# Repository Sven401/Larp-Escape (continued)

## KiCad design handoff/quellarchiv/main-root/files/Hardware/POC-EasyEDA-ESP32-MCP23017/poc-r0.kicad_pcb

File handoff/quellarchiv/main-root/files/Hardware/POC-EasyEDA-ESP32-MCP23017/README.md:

# ESP32–MCP23017-I²C-POC, Entwurf POC-R0

**Stand 2026-10-10:** elektrischer Vorentwurf, nicht gefertigt und nicht fertigungsbereit. `poc-r0.kicad_pcb` ist eine editierbare KiCad-5.1-PCB-Datei (Formatversion `20171130`) mit 19 Footprints, 116 Pads, 30 benannten Netzen und geschlossenem 110 × 80-mm-Umriss. **Sie hat null Leiterbahnen und Platzhalter-Footprints für SW1–SW3.** `netzliste.csv` ist eine von Hand erstellte Soll-Netzliste, kein CAD-Export. Die SVGs sind editierbare Vektoransichten, keine CAD-Schaltpläne. Es gibt noch keinen nativen EasyEDA-Pro-Schaltplan und kein ERC-Ergebnis. Der EasyEDA-DRC des importierten PCBs meldete 88 offene Verbindungen.

## Quellenbasis und Abgrenzung

- Produkt-Hauptcheckout `main` / `29da937c4309beddfd45c5dd0fbf84fdf853d8e4`, am 2026-10-10 geprüft. Die 15 älteren Dateien in `Hardware/` sind unveränderte Eingangsquellen; insbesondere ihre Beschriftungen belegen keine reale Originalbox-Verdrahtung.
- Vergleich: `.hardware-interface-worktree/Hardware/SCHNITTSTELLENABGLEICH-2026-10-10.md` auf `plan/hardware-revision-schnittstellenabgleich` / `853dd06423d52eec30d93f394b21280903c128d1`; Firmware-Pins in `.hardware-diagnostic-worktree/src/GameConfiguration/StandardProfile.cpp` und `lib/MCPConfig/MCPConfig.cpp` auf `db52d7aa318a96e24e97e6b62194df644b9758e2`. Der POC bildet **einen** Expander ab, nicht die zwei Expander der Originalbox.
- [Espressif DevKitC V4, Steckerbelegung und Versorgung](https://docs.espressif.com/projects/esp-dev-kits/en/latest/esp32/esp32-devkitc/user_guide.html), [ESP32-WROOM-32E](https://documentation.espressif.com/esp32-wroom-32e_esp32-wroom-32ue_datasheet_en.html), [ESP32-Hardware-Designrichtlinien](https://documentation.espressif.com/esp-hardware-design-guidelines/en/latest/esp32/index.html), [Microchip MCP23017 DS20001952D](https://ww1.microchip.com/downloads/aemDocuments/documents/APID/ProductDocuments/DataSheets/MCP23017-Data-Sheet-DS20001952.pdf).
- EasyEDA Pro V3.2.149 ist als lokale GUI verfügbar. Am 2026-10-10 wurde `poc-r0.kicad_pcb` über **Import > KiCad** in ein EasyEDA-Pro-Projekt `poc-r0` importiert. Umriss, Footprints und Ratlines waren in der PCB-Ansicht sichtbar. Der Import ist keine vollständige elektrische oder mechanische Validierung. Die Bridge-Erweiterung v0.1.1 wurde ebenfalls importiert, ihre externe Interaktionsberechtigung ist jedoch nicht freigeschaltet; `easyeda_doctor` meldete deshalb `disconnected` am lokalen Port 18765. Eine CLI wurde nicht gefunden. Das [V3-Dateiformat](https://prodocs.easyeda.com/en/format/index/) ist ein projektgebundenes Logformat; die kanonische PoC-Quelle bleibt bis zu einem geprüften nativen Export die KiCad-Datei.

## Architekturentscheidung

X1 ist **ESP32-DevKitC V4 mit ESP32-WROOM-32E**, als steckbare Baugruppe auf zwei 19-poligen Buchsenleisten. Der DevKit übernimmt USB, Spannungsregler, USB-UART und seine vorhandenen EN-/BOOT-Funktionen. Diese Entscheidung vermeidet im POC ein ungeprüftes eigenes HF-Layout für das WROOM-Modul. Ein beliebiges als „ESP32 DevKit“ verkauftes Board ist kein freigegebener Ersatz: Steckerabstand, Bestückungsseite und USB-Überstand sind vor dem PCB-Footprint gegen genau das beschaffte DevKit und Espressifs Maßzeichnung zu prüfen.

X1 wird ausschließlich über seinen USB-Anschluss versorgt. Der 5-V-Stift J2/19 des DevKit bleibt unbeschaltet. U1 (MCP23017-E/SP, 28-poliges SPDIP) erhält 3,3 V von X1 J2/1. Keine externe 3,3-V-Einspeisung, kein 5-V-I/O und keine Leistungslast an den GPIO-Klemmen. Der verfügbare 3,3-V-Strom des konkret beschafften DevKit und die Last des späteren Aufbaus sind noch nicht gemessen oder budgetiert; die POC-Klemmen sind nur für hochohmige Logik-/Messanschlüsse vorgesehen.

SDA = ESP GPIO21, SCL = GPIO22, beide mit je 4,7 kΩ nach 3,3 V. Das entspricht der geprüften Firmware-Konfiguration. U1 A2/A1 liegen auf GND; A0 hat 10 kΩ Pulldown. Ohne Shunt JP1: 0x20; mit JP1 nach 3,3 V: 0x21. JP1 darf nur spannungslos umgesteckt werden. Der Firmwarestand der Originalbox erwartet gleichzeitig 0x20 und 0x21; ein Lauf dieser Firmware auf diesem POC würde daher keine vollständige Box simulieren.

SW1 zieht X1 EN nach GND (Reset), SW2 zieht GPIO0 nach GND (Boot), SW3 zieht U1 RESET nach GND. R3/R5/R6 sind je 10 kΩ Pull-ups; R5/R6 ergänzen die DevKit-Beschaltung und müssen gegen das genaue Board-Schaltbild geprüft werden. C1 100 nF direkt an U1 VDD/VSS, C2 10 µF an der lokalen 3,3-V-Schiene. Keine Interruptleitung ist zum ESP verdrahtet; INTA/INTB sind nur auf J5 herausgeführt. Sie brauchen vor Nutzung eine definierte elektrische Konfiguration und bei Open-Drain-Betrieb einen Pull-up.

## Pin-/Bus-/Versorgungsvertrag POC-HW/0.1-draft

| Signal | Quelle → Ziel | Pegel / Richtung | Status |
| --- | --- | --- | --- |
| +3V3 | X1 DevKit J2/1 → U1/9, Pull-ups, C1/C2 | 3,3 V, USB-abgeleitet | Entwurf; Stromreserve offen |
| GND | X1 J2/14 und J3/1,7 → U1/10, Taster, C1/C2 | gemeinsamer Rückleiter | Entwurf |
| SDA | X1 J3/6 GPIO21 → U1/13 | I²C, Open Drain, 4,7 kΩ nach 3,3 V | Quellkonfiguration abgeglichen |
| SCL | X1 J3/3 GPIO22 → U1/12 | I²C, 4,7 kΩ nach 3,3 V | Quellkonfiguration abgeglichen |
| EN / BOOT | X1 J2/2 / J3/14 → SW1 / SW2 nach GND | aktive LOW-Taster; GPIO0 ist Strap-Pin | nur POC, nicht Boxbeleg |
| MCP_RESET | U1/18 → SW3 nach GND, R3 nach 3,3 V | aktiv LOW | Entwurf |
| A0/A1/A2 | U1/15 /16 /17 | 0x20 oder 0x21 per JP1; A1=A2=LOW | Entwurf |
| GPA0…GPA7 | U1/21…28 → J3/1…8 | 3,3-V-GPIO | GPA7 laut Microchip nur als Ausgang einplanen |
| GPB0…GPB7 | U1/1…8 → J4/1…8 | 3,3-V-GPIO | GPB7 laut Microchip nur als Ausgang einplanen |
| INTA/INTB | U1/20 /19 → J5/1 /2 | noch kein Pull-up/ESP-Eingang | Fähigkeit offen |
| ESP-GPIO23/19/18/17 | X1 J3/2/8/9/11 → J6/1…4 | 3,3-V-GPIO | POC-Breakout; GPIO17 nur bei WROOM-Variante |

J5/3 = 3,3 V, J5/4 = GND; J6/5 = 3,3 V, J6/6 = GND. J3/J4 meinen die neuen POC-Ausgänge GPA/GPB; „X1 J3“ meint die DevKit-Buchsenleiste. Die Namen sind bewusst verschieden qualifiziert. GPIO6–11 des ESP sind Flash-Pins und werden nicht herausgeführt. GPA7/GPB7 sind nach Microchip-DS20001952D für MCP23017 als **Output only** gekennzeichnet: Für die Originalbox-Wake-Zuordnung auf GPB7 ist das ein offener Bauteil-/Firmwarekonflikt, kein hier stillschweigend gelöster Fehler.

## BOM, Netzliste und PCB-Ableitung

- `netzliste.csv`: vollständige Soll-Verbindungen der bestückten Teile; Semikolontrenner, UTF-8. `NC`-Zeilen bezeichnen absichtlich unbeschaltete Pins. Sie wurde gegen die obige Tabelle manuell verglichen, nicht aus einem CAD-System exportiert.
- `stueckliste.csv`: Soll-BOM mit offenen Beschaffungs-/Footprintfragen. X1 zählt als bestückte DevKit-Baugruppe; seine aufgelöteten Teile werden nicht doppelt bilanziert.
- `poc-r0.kicad_pcb`: editierbarer KiCad-5.1-PCB-Entwurf mit Pads, Netzen und Umriss; 0 Segmente/Vias/Zonen. Der DevKit-Buchsenabstand ist im Entwurf 25,4 mm, entsprechend [Espressifs Maßblatt](https://dl.espressif.com/dl/schematics/esp32_devkitc_v4_dimensions.pdf); die Orientierung und reale Passung des konkret beschafften Boards bleiben ungeprüft. Die Gehäuseumrisse der Buchsen und Taster sind vereinfachte Platzhalter, keine freigegebenen Bibliotheksfootprints.
- `schaltbild.svg` und `pcb-platzierung.svg`: editierbare Vektoransichten für Schaltungsabsicht und Anordnung. Die PCB-Skizze enthält keine fertigungstauglichen Daten; die KiCad-Datei ist die maßgebliche PCB-Quelle.
- `pruefe_quellen.py`: syntaktischer Abgleich von KiCad-Pads, Soll-Netzliste, CSV und SVG; **kein CAD-Parser und keine DRC**. Vor einem Layoutabschluss muss ein PCB-Designer die DevKit-Mechanik, U1-Footprint und Steckerausrichtung im CAD prüfen, einen nativen Schaltplan anlegen, den PCB routen und ERC/DRC ausführen.

## Prüfstand und Freigabetor

Durchgeführt: Vergleich der offiziellen Pinbelegungen mit Firmware-Konfiguration und Quellenbericht; Abgleich der aktuellen Android-Diagnosequelle `.diagnose-android-fake-worktree/companion/android/DIAGNOSTIC-V1.md` (synthetischer Diagnosepfad, keine POC-Fähigkeit); `python Hardware/POC-EasyEDA-ESP32-MCP23017/pruefe_quellen.py` erfolgreich: 19 Footprints, 116 Pads, 88 zugeordnete Pads identisch zur Soll-Netzliste, 31 Netzeinträge, 12 BOM-Zeilen, zwei parsebare SVGs. Der Test prüft nur Struktur und Zuordnung. EasyEDA-Pro-KiCad-Import gelang; der dortige DRC zeigte **88 Connection Errors** (offene Verbindungen) und keine darüber hinaus angezeigte Fehlerklasse. Nicht durchgeführt: ERC, Routing, mechanische Passprobe, USB-/3,3-V-Messung, I²C-Kommunikation, GPIO-Last- oder physischer Funktionsnachweis. **Fertigungsfreigabe: nein.** Die unterbrochene Originalbox-Prüfung bleibt unberührt. Ein späterer Nutzerlauf muss über App/Firmware geführt und erst nach Abschluss anhand des exportierten Berichts ausgewertet werden.

## Versions- und Änderungsnachweis

| Version | Datum | Änderung | Beleg-/Freigabestand |
| --- | --- | --- | --- |
| POC-HW/0.1-draft | 2026-10-10 | Eigenständiger 3,3-V-DevKitC-V4/Ein-MCP-POC mit 0x20/0x21-Jumper, EN/BOOT/MCP-Reset und GPIO-Ausgängen; KiCad-5.1-PCB mit Pads/Netzen/Umriss | EasyEDA-KiCad-Import und Strukturabgleich bestanden; 88 offene DRC-Verbindungen; ungeroutet, kein ERC oder Gerätetest; keine Firmware-/App-Implementierung |

Bei einer späteren Pin-, Pegel-, Adress-, Strom- oder Fähigkeitsänderung diese Tabelle und die Netzliste zusammen versionieren und die dann aktuellen Firmware- und App-Quellen erneut abgleichen. Der Vertrag beschreibt nur den POC und darf nicht als Änderung der Originalbox-Konfiguration übernommen werden.

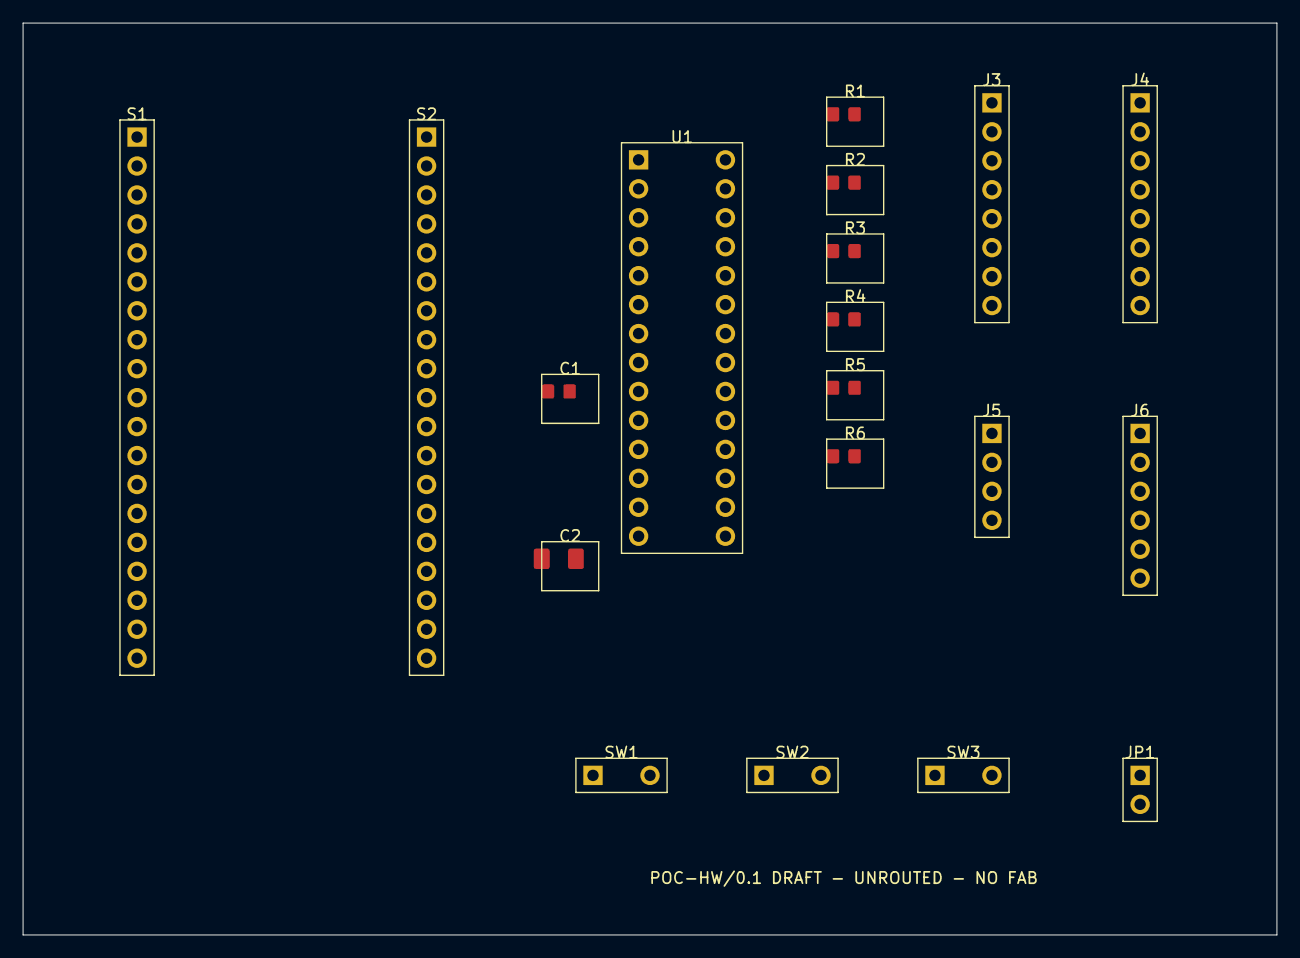
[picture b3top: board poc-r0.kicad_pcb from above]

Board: 2 copper layers, 110.0 x 80.0 mm, 19 parts (0 on the bottom side), 30 nets, no tracks yet.

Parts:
C1: 100n; C_0805_2012Metric
C2: 10u; C_1206_3216Metric
J3: J3; PinHeader_1x08_P2.54mm_Vertical
J4: J4; PinHeader_1x08_P2.54mm_Vertical
J5: J5; PinHeader_1x04_P2.54mm_Vertical
J6: J6; PinHeader_1x06_P2.54mm_Vertical
JP1: JP1; PinHeader_1x02_P2.54mm_Vertical
R1, R2: 4k7; R_0805_2012Metric
R3, R4, R5, R6: 10k; R_0805_2012Metric
S1: DevKitC J2; DevKitC_J2_1x19
S2: DevKitC J3; DevKitC_J3_1x19
SW1: SW1; SW_SPST_placeholder
SW2: SW2; SW_SPST_placeholder
SW3: SW3; SW_SPST_placeholder
U1: MCP23017-E/SP; DIP-28_W7.62mm

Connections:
+3V3: C1.1, C2.1, J5.3, J6.5, JP1.2, R1.1, R2.1, R3.1, R5.1, R6.1, S1.1, U1.9
BOOT: R6.2, S2.14, SW2.1
EN: R5.2, S1.2, SW1.1
ESP_GPIO17: J6.4, S2.11
ESP_GPIO18: J6.3, S2.9
ESP_GPIO19: J6.2, S2.8
ESP_GPIO23: J6.1, S2.2
GND: C1.2, C2.2, J5.4, J6.6, R4.2, S1.14, S2.1, S2.7, SW1.2, SW2.2, SW3.2, U1.10, U1.16, U1.17
GPA0: J3.1, U1.21
GPA1: J3.2, U1.22
GPA2: J3.3, U1.23
GPA3: J3.4, U1.24
GPA4: J3.5, U1.25
GPA5: J3.6, U1.26
GPA6: J3.7, U1.27
GPA7: J3.8, U1.28
GPB0: J4.1, U1.1
GPB1: J4.2, U1.2
GPB2: J4.3, U1.3
GPB3: J4.4, U1.4
GPB4: J4.5, U1.5
GPB5: J4.6, U1.6
GPB6: J4.7, U1.7
GPB7: J4.8, U1.8
INTA: J5.1, U1.20
INTB: J5.2, U1.19
MCP_A0: JP1.1, R4.1, U1.15
MCP_RESET: R3.2, SW3.1, U1.18
SCL: R2.2, S2.3, U1.12
SDA: R1.2, S2.6, U1.13

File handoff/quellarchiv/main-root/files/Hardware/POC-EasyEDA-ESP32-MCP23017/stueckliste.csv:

Referenz;Anzahl;Wert/Typ;Bauform;Funktion;Beschaffung/Prüfpunkt
X1;1;ESP32-DevKitC V4 mit ESP32-WROOM-32E;Baugruppe 2x19 2.54mm;ESP32 USB Stromversorgung;konkrete Modul- und Steckerbestückung vor Footprint prüfen
U1;1;MCP23017-E/SP;SPDIP-28 300mil;I2C GPIO Expander;exakte Package-/Pinvariante prüfen
S1 S2;2;Buchsenleiste 1x19 2.54mm;THT;X1 Aufnahme;Abstand und Orientierung offen
J3 J4;2;Stiftleiste 1x8 2.54mm;THT;GPA und GPB;Steckertyp offen
J5;1;Stiftleiste 1x4 2.54mm;THT;INTA INTB Versorgung;Steckertyp offen
J6;1;Stiftleiste 1x6 2.54mm;THT;ESP GPIOs Versorgung;Steckertyp offen
JP1;1;Stiftleiste 1x2 mit Shunt;THT;MCP A0 Adresswahl;Shunt nur spannungslos
R1 R2;2;4.7k 1%;0805;I2C Pull-ups;Buskapazität und vorhandene Pull-ups vor Bestückung prüfen
R3 R4 R5 R6;4;10k 1%;0805;RESET A0 EN BOOT Bias;DevKit Schaltung auf doppelte Bias prüfen
C1;1;100nF X7R >=6.3V;0805;U1 Entkopplung;nah an U1/9 und U1/10
C2;1;10uF X7R >=6.3V;1206;lokaler 3.3V Puffer;Derating prüfen
SW1 SW2 SW3;3;Taster NO momentary;THT oder SMD offen;EN BOOT MCP_RESET;Footprint vor PCB festlegen
